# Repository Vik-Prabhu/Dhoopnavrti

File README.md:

# Dhoopnavarti
Project for a Ayurvedic Medical Ear cleaning device. This device needed temperature and pressure to be monitored and displayed on an oled display. We used STM32L432 MCU for this purpose. Along with these sensores we made a battery monitoring system with the MCU by reading analog values from the battery and displaying it on the oled. The device also readed a charging port of a lighter and the battery for which we used a battery charger with USB. This Repo Includes the PCB designs of the project.

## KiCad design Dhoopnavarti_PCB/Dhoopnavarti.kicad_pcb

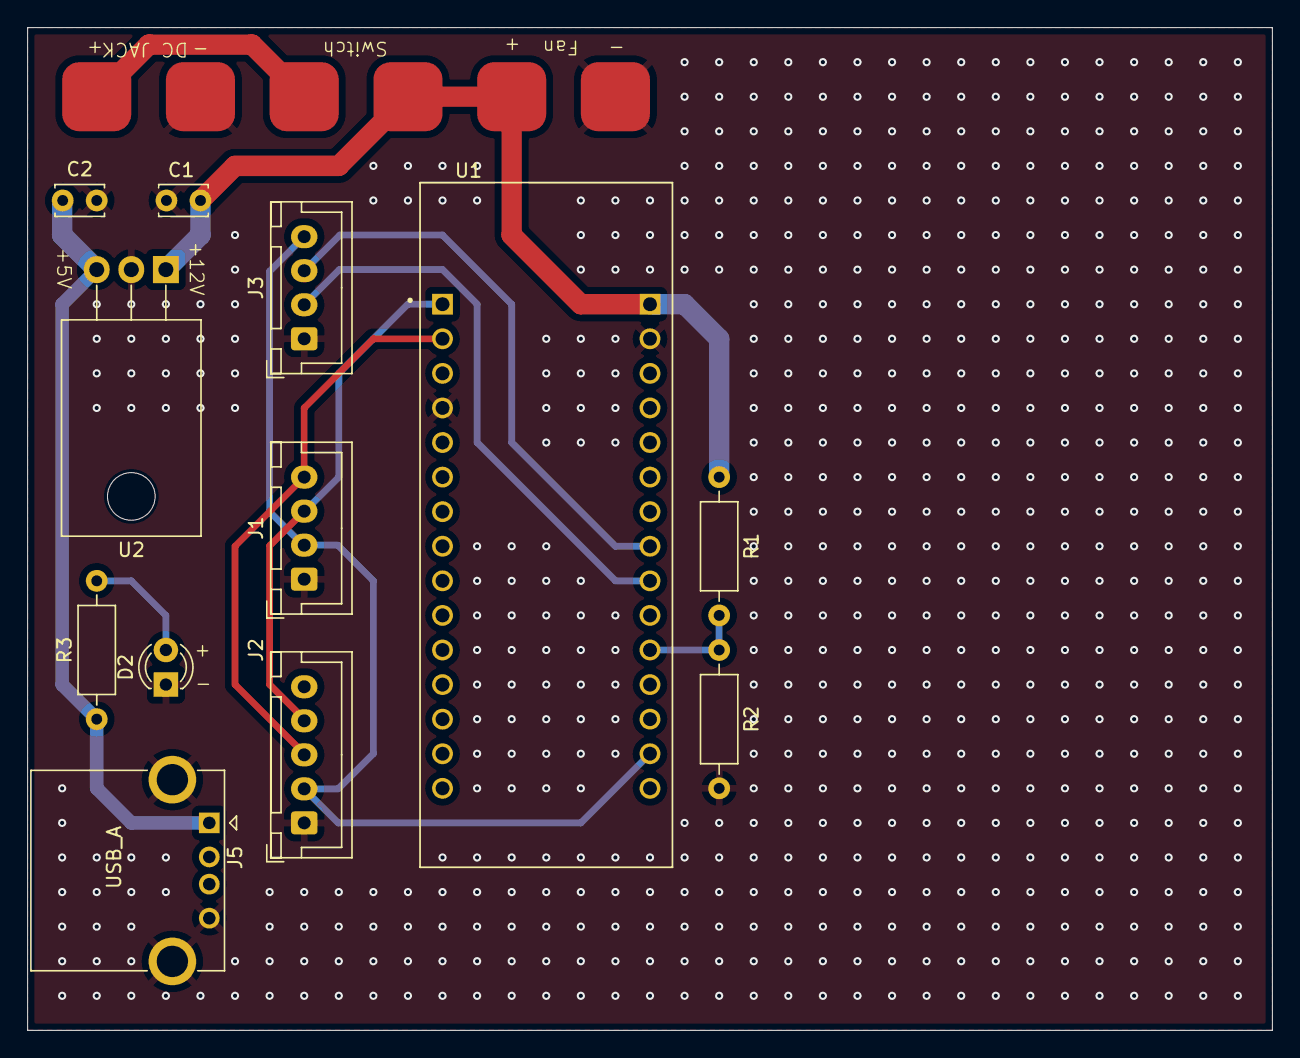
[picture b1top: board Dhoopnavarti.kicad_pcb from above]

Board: 2 copper layers, 91.4 x 73.7 mm, 15 parts (0 on the bottom side), 11 nets.

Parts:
C1: 330nF; C_Disc_D3.4mm_W2.1mm_P2.50mm
C2: 100nF; C_Disc_D3.4mm_W2.1mm_P2.50mm
D2: LED; LED_D3.0mm
DC JACK: Screw_Terminal_01x02; Wire_Pad
Fan: Screw_Terminal_01x02; Wire_Pad
J1, J3: Conn_01x04_Pin; JST_XH_B4B-XH-A_1x04_P2.50mm_Vertical
J2: Conn_01x05_Pin; JST_XH_B5B-XH-A_1x05_P2.50mm_Vertical
J5: USB_A; USB_A_Kycon_KUSBX-AS1N-B_Horizontal
R1, R2: R_US; R_Axial_DIN0207_L6.3mm_D2.5mm_P10.16mm_Horizontal
R3: 220; R_Axial_DIN0207_L6.3mm_D2.5mm_P10.16mm_Horizontal
Switch: Screw_Terminal_01x02; Wire_Pad
U1: NUCLEO-L432KC; MODULE_NUCLEO-L432KC
U2: LM7805_TO220; TO-220-3_Horizontal_TabDown

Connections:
+3.3V: J1.2, J2.2, J3.4, U1.CN4_14 (+3V3)
+5V: C2.1, J5.1 (VBUS), R3.1, U2.3 (VO)
+12V: C1.1, Fan.1, R1.1, Switch.2, U1.CN4_1 (VIN), U2.1 (VI)
Battery_+12V: DC JACK.1, Switch.1
GND: C1.2, C2.2, D2.1 (K), DC JACK.2, Fan.2, J1.1, J2.1, J3.1, J5.4 (GND), J5.5 (Shield), R2.2, U1.CN3_4 (GND_CN3), U1.CN4_2 (GND_CN4), U2.2 (GND)
unnamed: D2.2 (A), R3.2
unnamed: R1.2, R2.1, U1.CN4_11 (PA1)
OUT: J3.3, U1.CN4_8 (PA5)
SCK: J3.2, U1.CN4_9 (PA4)
SCL: J1.3, J2.4, U1.CN3_1 (PA9)
SDA: J1.4, J2.3, U1.CN3_2 (PA10)

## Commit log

2024-11-11 Pressure Sensor v0.1
2024-11-14 Sensor Fusion
2024-11-14 Sensor Fusion v1.00
2024-11-15 Battery Monitor v1.01
2025-01-05 PCB File Added
2025-01-11 Routing v1
2025-01-17 Battery Monitor v2
